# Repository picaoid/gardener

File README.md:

# gardener
Ardunio based programmable garden irrigation system. Working in progress.

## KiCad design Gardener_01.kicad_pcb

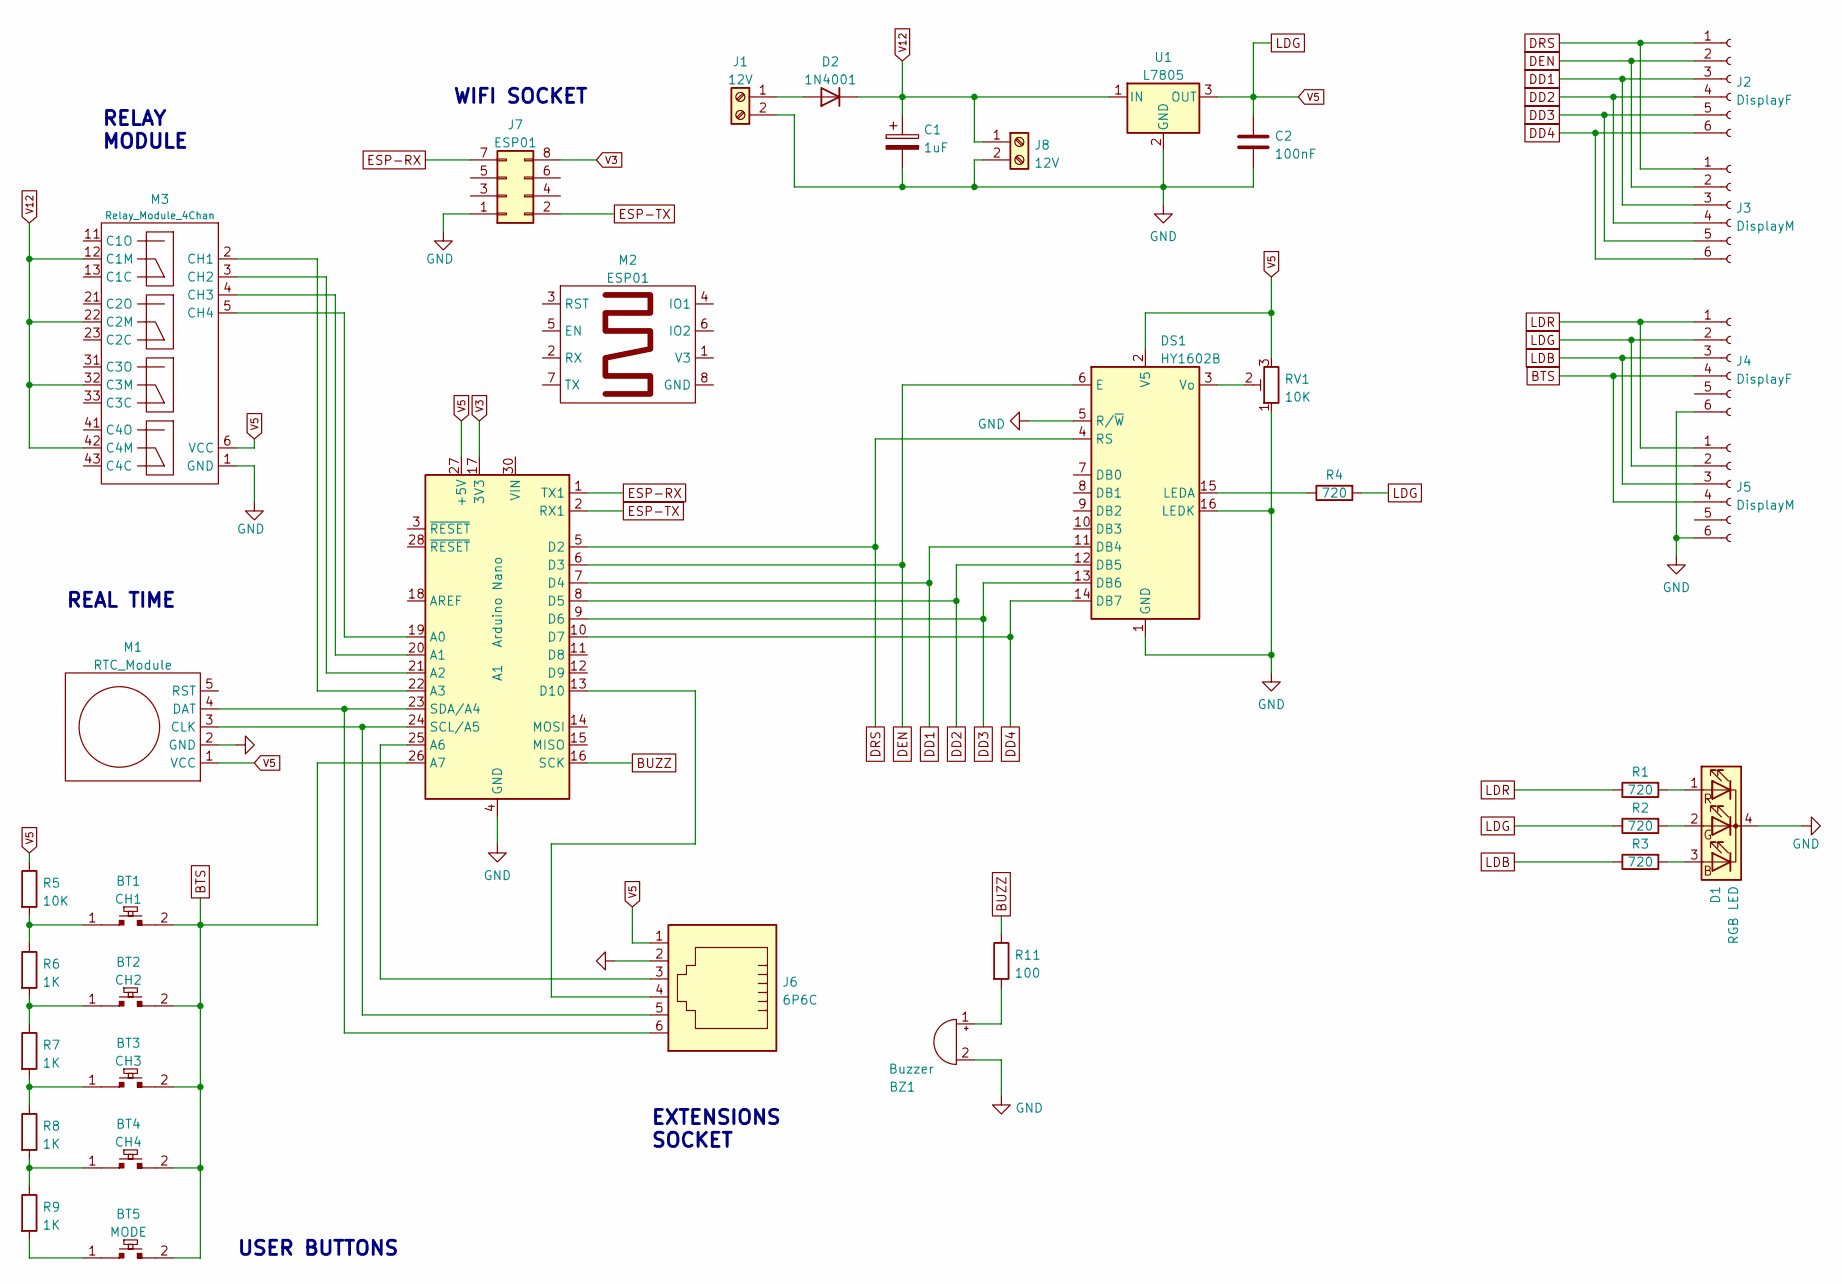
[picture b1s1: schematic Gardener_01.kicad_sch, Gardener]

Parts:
A1: Arduino Nano; Arduino_Nano
BT1: CH1; Tactile_12_SPST
BT2: CH2; Tactile_12_SPST
BT3: CH3; Tactile_12_SPST
BT4: CH4; Tactile_12_SPST
BT5: MODE; Tactile_12_SPST
BZ1: Buzzer; Buzzer_12x9.5RM7.6
C1: 1uF; CP_Radial_D5.0mm_P2.50mm
C2: 100nF; C_Disc_D6.0mm_W2.5mm_P5.00mm
D1: RGB LED; LED_D5.0mm-4_RGB_Wide_Pins
D2: 1N4001; D_DO-41_SOD81_P10.16mm_Horizontal
DS1: HY1602B; HY-1602B-pica
J1: 12V; BarrelJack_CUI_PJ-063AH_Horizontal_CircularHoles
J2, J4: DisplayF; PinSocket_1x06_P2.54mm_Vertical
J3, J5: DisplayM; PinSocket_1x06_P2.54mm_Vertical
J6: 6P6C; RJ12_pica
J7: ESP01; PinSocket_2x04_P2.54mm_Horizontal
J8: 12V; TerminalBlock_bornier-2_P5.08mm
M1: RTC_Module
M2: ESP01; ESP01_Module
M3: Relay_Module_4Chan; RelaysModule_4
R1, R2, R3, R4: 720; R_Axial_DIN0207_L6.3mm_D2.5mm_P7.62mm_Horizontal
R5: 10K; R_Axial_DIN0207_L6.3mm_D2.5mm_P7.62mm_Horizontal
R6, R7, R8, R9: 1K; R_Axial_DIN0207_L6.3mm_D2.5mm_P7.62mm_Horizontal
R11: 100; R_Axial_DIN0207_L6.3mm_D2.5mm_P15.24mm_Horizontal
RV1: 10K; Potentiometer_ACP_CA9-V10_Vertical
U1: L7805; TO-220-3_Horizontal_TabDown

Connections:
BTS: A1.26 (A7), BT1.2, BT2.2, BT3.2, BT4.2, BT5.2, J4.4, J5.4
BUZZ: A1.16 (SCK), R11.1
DD1: A1.7 (D4), DS1.11 (DB4), J2.3, J3.3
DD2: A1.8 (D5), DS1.12 (DB5), J2.4, J3.4
DD3: A1.9 (D6), DS1.13 (DB6), J2.5, J3.5
DD4: A1.10 (D7), DS1.14 (DB7), J2.6, J3.6
DEN: A1.6 (D3), DS1.6 (E), J2.2, J3.2
DRS: A1.5 (D2), DS1.4 (RS), J2.1, J3.1
ESP-RX: A1.1 (TX1), J7.7
ESP-TX: A1.2 (RX1), J7.2
GND: A1.4 (GND), A1.29 (GND), BZ1.2 (+), C1.2, C2.2, D1.4 (K), DS1.1 (GND), DS1.5 (R/~W), DS1.16 (LEDK), J1.2, J4.6, J5.6, J6.2, J7.1, J8.2, M1.2 (GND), M3.1 (GND), RV1.1, U1.2 (GND)
LDB: J4.3, J5.3, R3.1
LDG: A1.27 (+5V), C2.1, DS1.2 (V5), J4.2, J5.2, J6.1, M1.1 (VCC), M3.6 (VCC), R2.1, R4.2, R5.1, RV1.3, U1.3 (OUT)
LDR: J4.1, J5.1, R1.1
unnamed: A1.13 (D10), J6.4
unnamed: A1.19 (A0), M3.5 (CH4)
unnamed: A1.20 (A1), M3.4 (CH3)
unnamed: A1.21 (A2), M3.3 (CH2)
unnamed: A1.22 (A3), M3.2 (CH1)
unnamed: A1.23 (SDA/A4), J6.6, M1.4 (DAT)
unnamed: A1.24 (SCL/A5), J6.5, M1.3 (CLK)
unnamed: A1.25 (A6), J6.3
unnamed: BT1.1, R5.2, R6.1
unnamed: BT2.1, R6.2, R7.1
unnamed: BT3.1, R7.2, R8.1
unnamed: BT4.1, R8.2, R9.1
unnamed: BT5.1, R9.2
unnamed: BZ1.1 (-), R11.2
unnamed: D1.1 (RA), R1.2
unnamed: D1.2 (GA), R2.2
unnamed: D1.3 (BA), R3.2
unnamed: D2.2 (A), J1.1
unnamed: DS1.3 (Vo), RV1.2
unnamed: DS1.15 (LEDA), R4.1
V3: A1.17 (3V3), J7.8
V12: C1.1, D2.1 (K), J8.1, M3.12 (C1M), M3.22 (C2M), M3.32 (C3M), M3.42 (C4M), U1.1 (IN)

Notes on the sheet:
WIFI SOCKET
REAL TIME
EXTENSIONS SOCKET
RELAY MODULE
USER BUTTONS

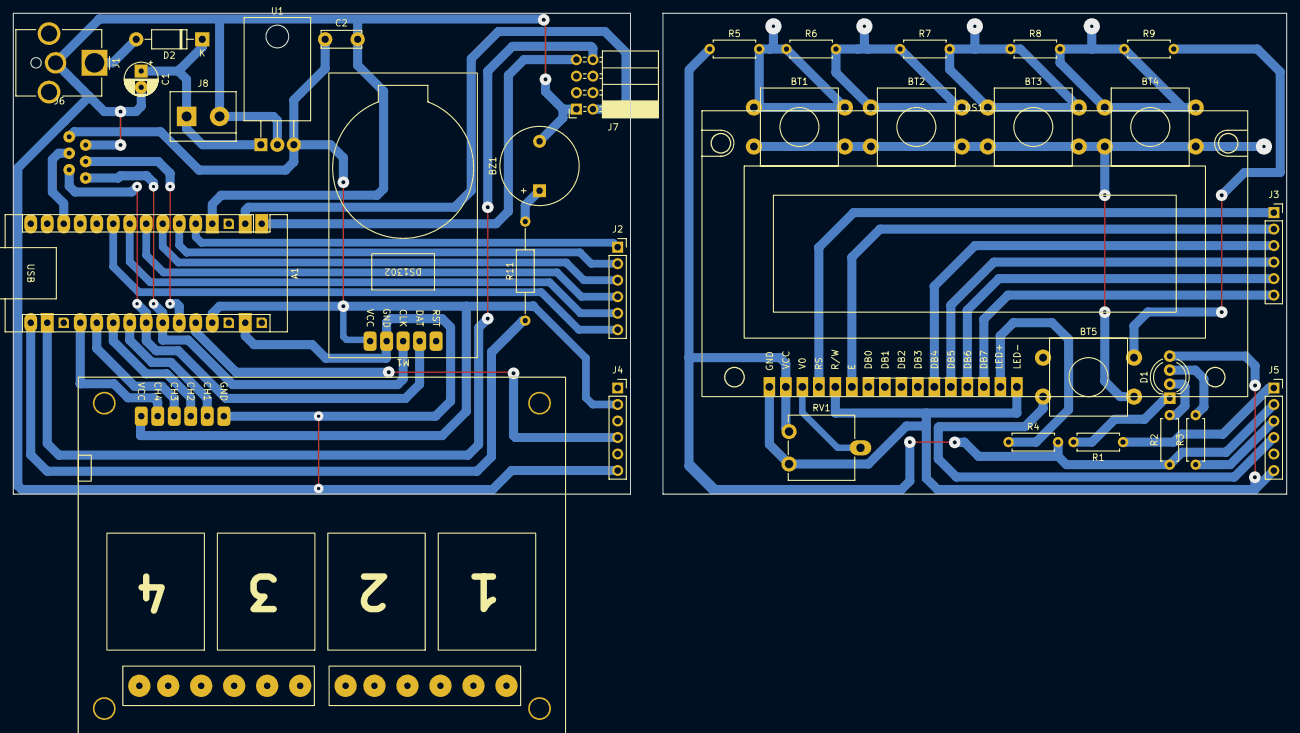
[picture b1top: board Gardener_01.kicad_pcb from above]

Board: 2 copper layers, 196.0 x 74.0 mm, 34 parts (0 on the bottom side), 36 nets.
